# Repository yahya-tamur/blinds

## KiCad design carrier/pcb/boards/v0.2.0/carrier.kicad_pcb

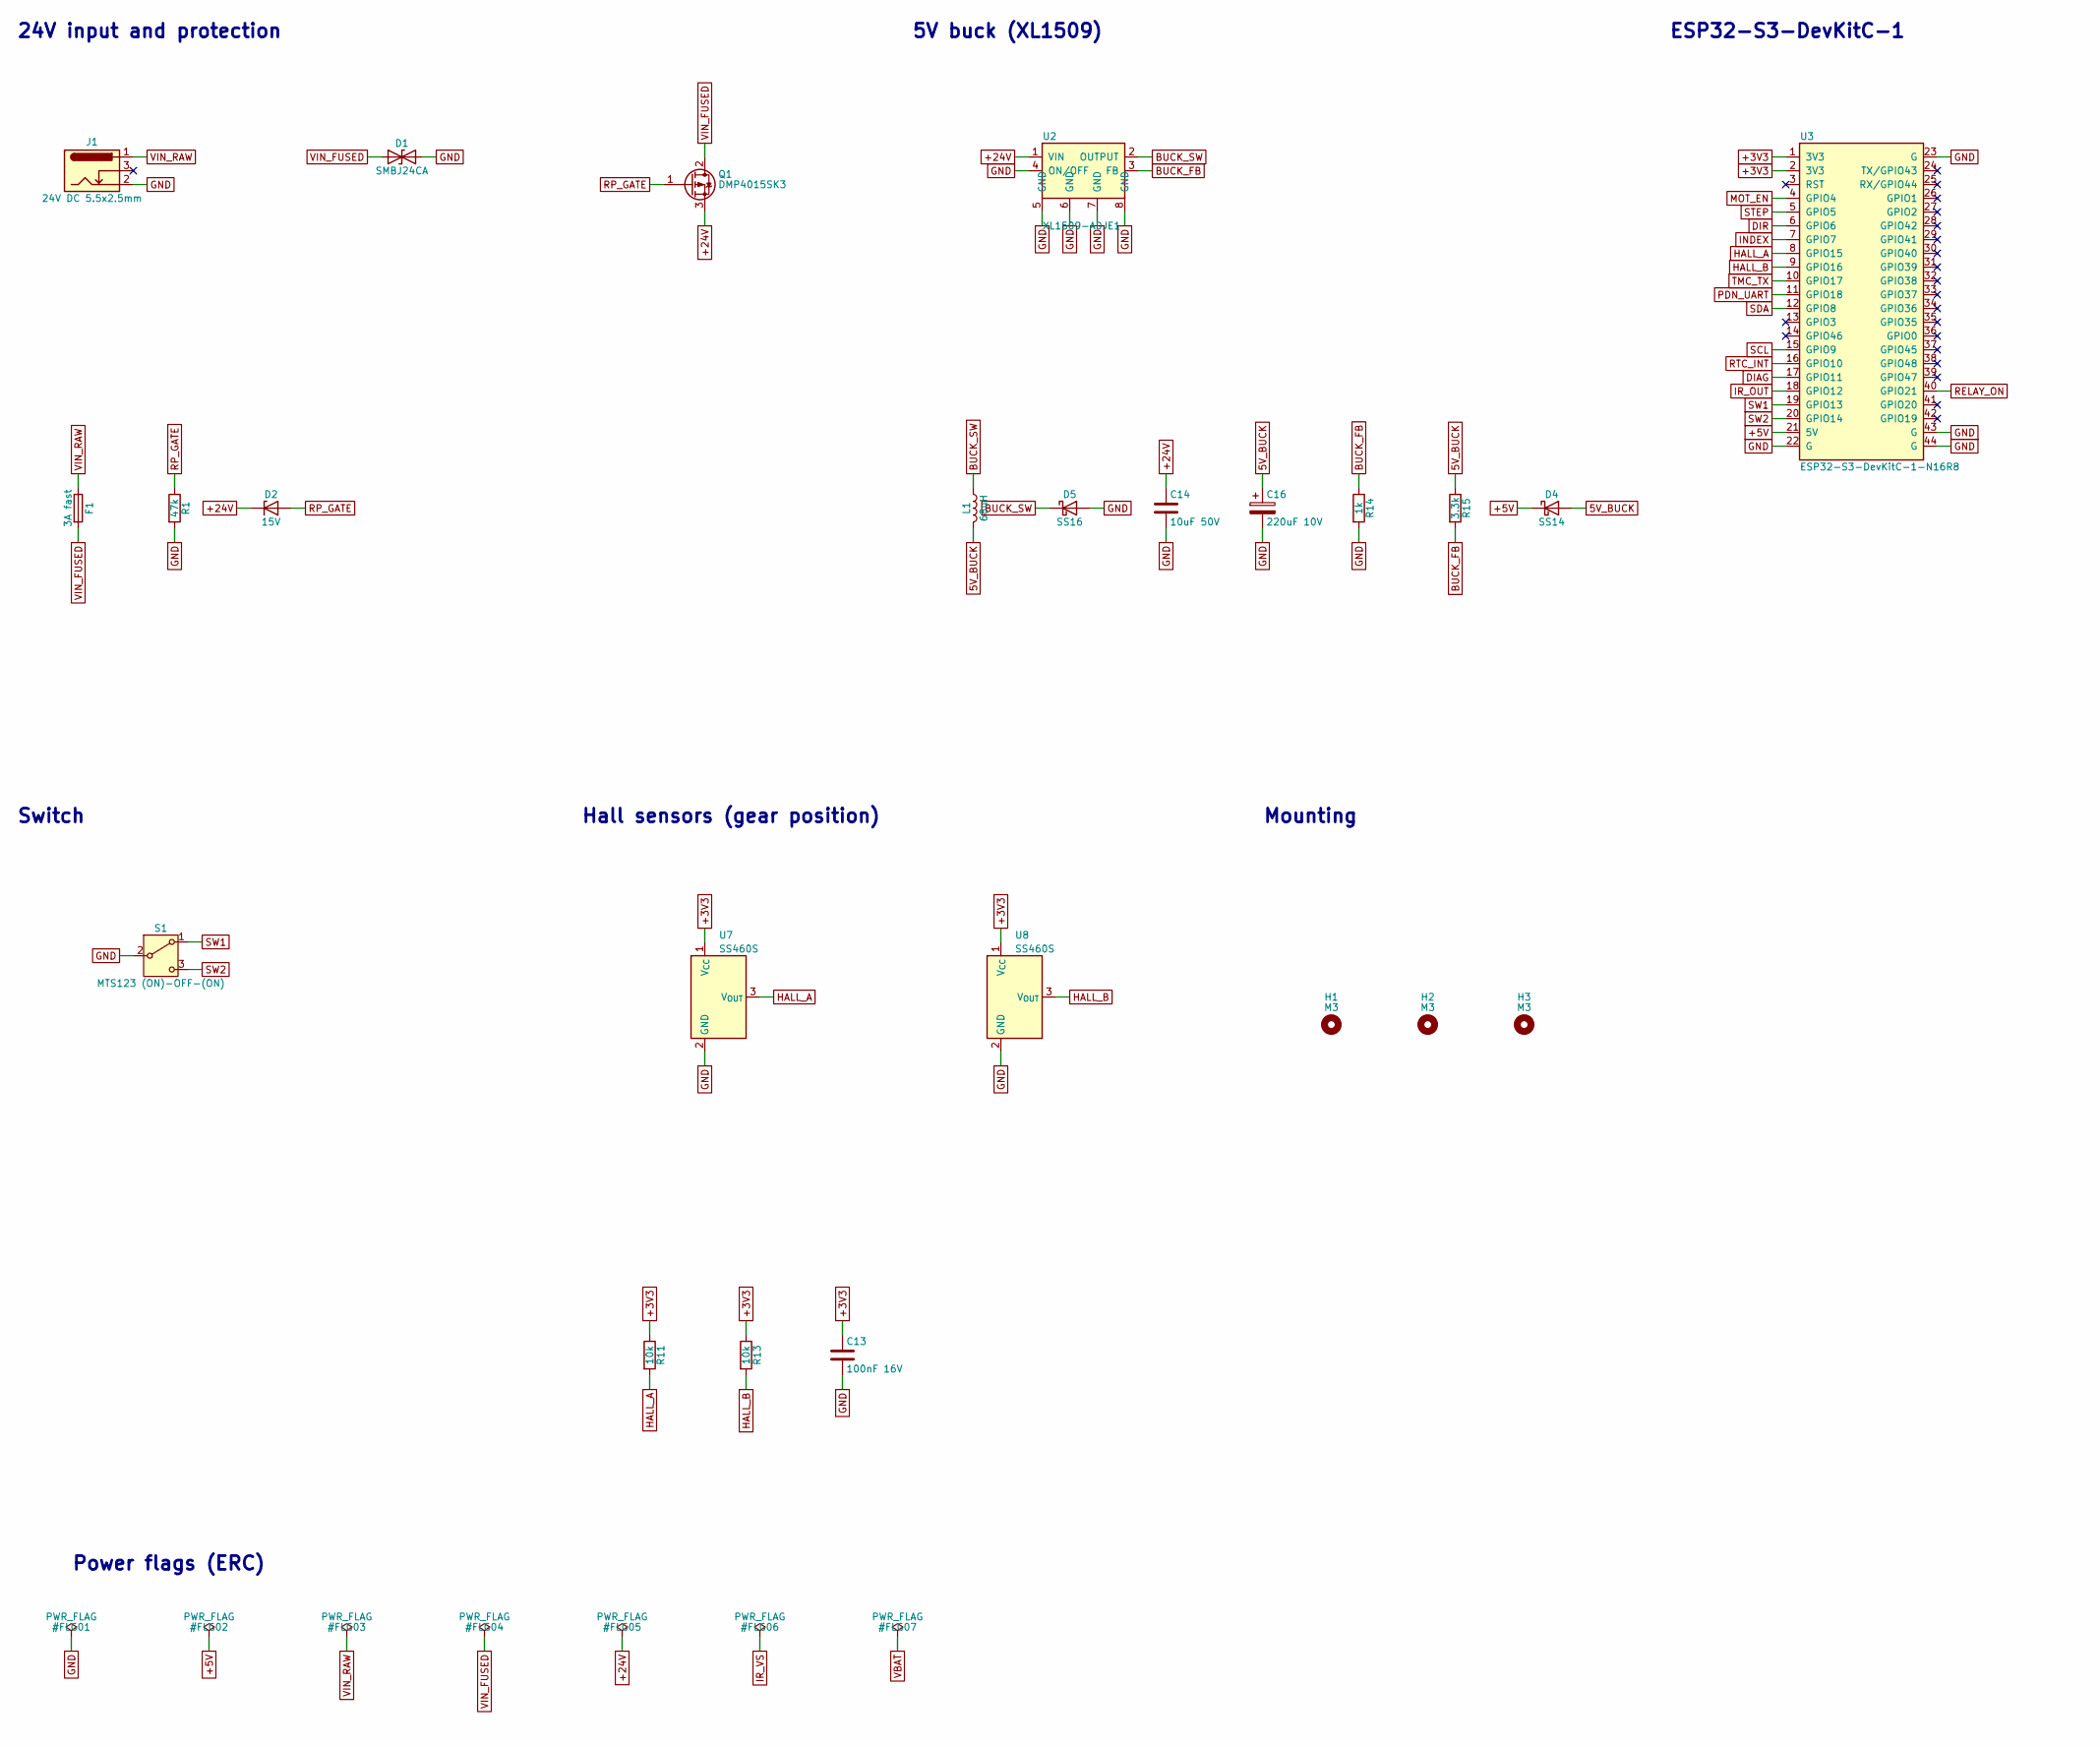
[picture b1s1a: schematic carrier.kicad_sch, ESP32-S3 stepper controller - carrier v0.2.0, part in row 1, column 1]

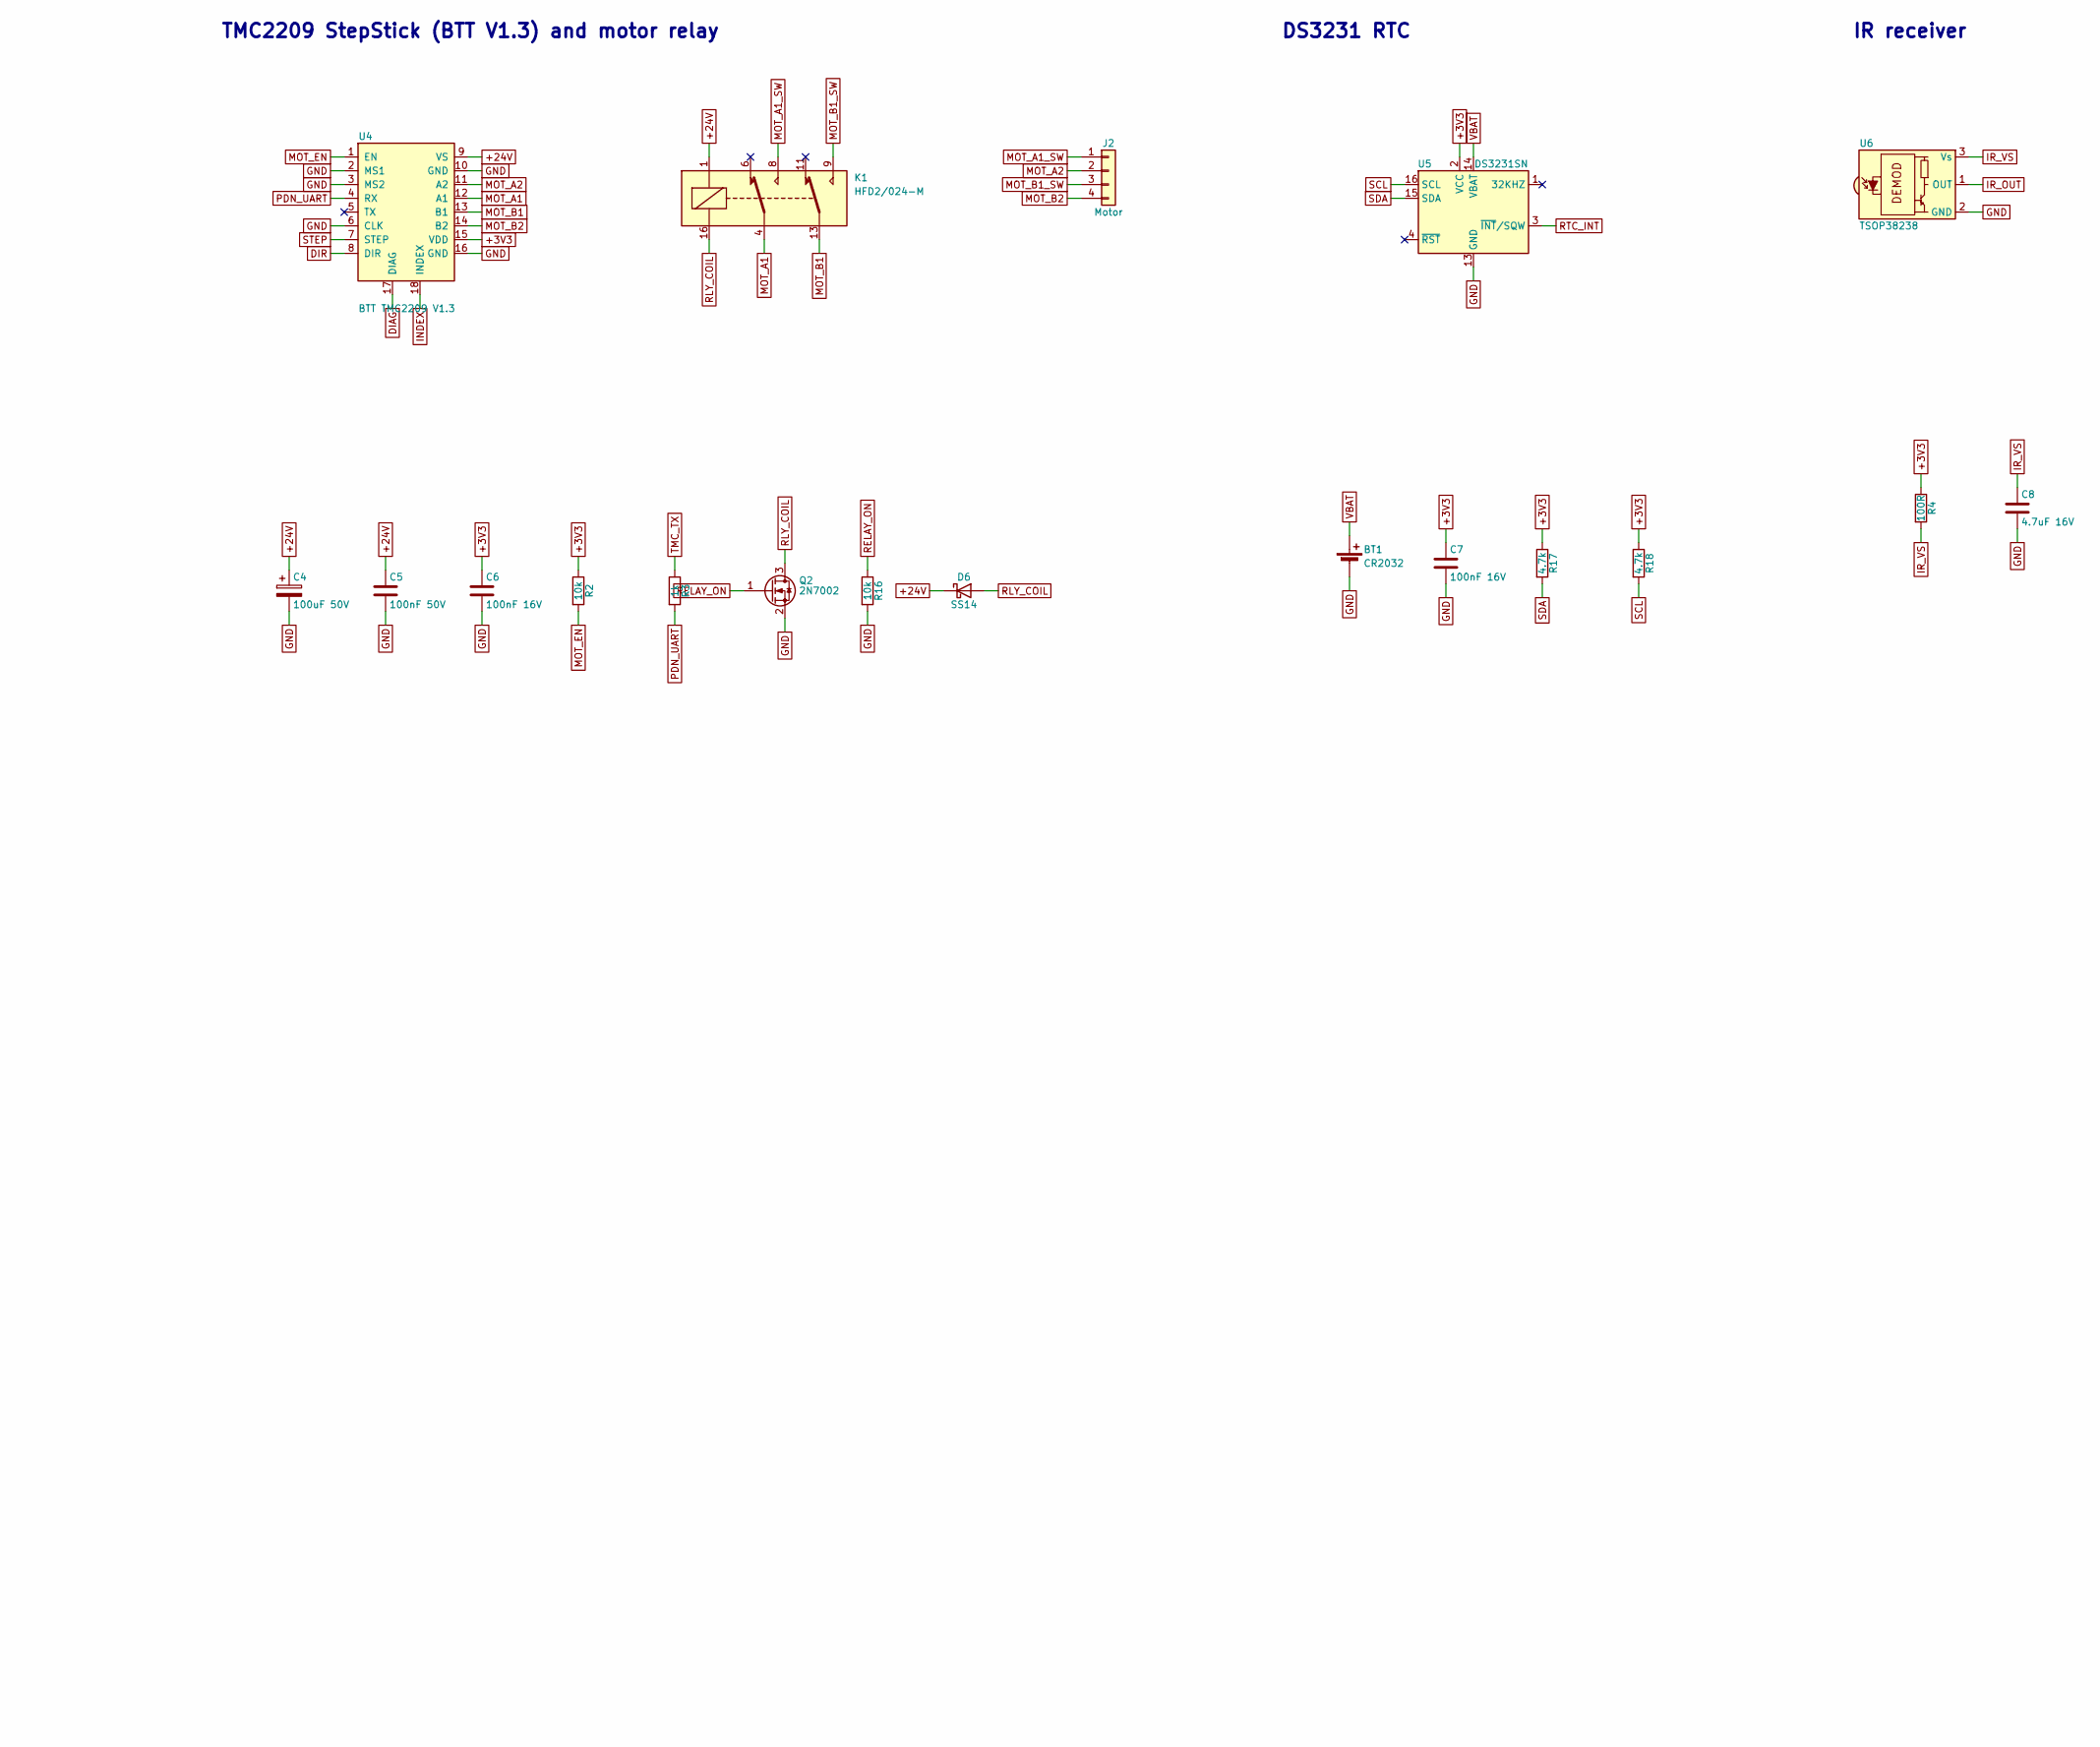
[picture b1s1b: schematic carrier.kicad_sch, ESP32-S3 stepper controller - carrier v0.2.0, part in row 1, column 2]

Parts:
BT1: CR2032; BatteryHolder_MYOUNG_BS-02-A1AJ010; MPN BS-02-A1AJ010; LCSC C5239862
C4: 100uF 50V; CP_Elec_8x10; MPN EEE-FK1H101P; LCSC C178548
C5: 100nF 50V; C_0805_2012Metric; LCSC C49678
C6, C7, C13: 100nF 16V; C_0805_2012Metric; LCSC C49678
C8: 4.7uF 16V; C_0805_2012Metric; LCSC C1779
C14: 10uF 50V; C_1210_3225Metric; MPN CL32B106KBJNNNE; LCSC C138687
C16: 220uF 10V; CP_Elec_6.3x5.4; MPN FVH010ADA221M0654; LCSC C7469982
D1: SMBJ24CA; D_SMB; MPN SMBJ24CA; LCSC C83268
D2: 15V; D_SOD-123; MPN MMSZ5245B; LCSC C2126
D4, D6: SS14; D_SMA; MPN SS14; LCSC C2480
D5: SS16; D_SMA; MPN SS16; LCSC C2481
F1: 3A fast; Fuse_Littelfuse-NANO2-451_453; MPN 0453003.MR; LCSC C178991
H1, H2, H3: M3; MountingHole_3.2mm_M3
J1: 24V DC 5.5x2.5mm; BarrelJack_DC-005_2.5mm_Horizontal_EdgeMount; MPN DC-005-5A-2.5; LCSC C381115
J2: Motor; JST_XH_S4B-XH-A_1x04_P2.50mm_Horizontal; MPN S4B-XH-A; LCSC C157925
K1: HFD2/024-M; Relay_DPDT_Hongfa_HFD2; MPN HFD2/024-M; LCSC C18198081
L1: 68uH; L_Changjiang_FNR6045S; MPN FNR6045S680MT; LCSC C168091
Q1: DMP4015SK3; TO-252-2; MPN DMP4015SK3-13; LCSC C513222
Q2: 2N7002; SOT-23; MPN 2N7002; LCSC C8545
R1: 47k; R_0805_2012Metric; LCSC C17713
R2, R11, R13, R16: 10k; R_0805_2012Metric; LCSC C17414
R3, R14: 1k; R_0805_2012Metric; LCSC C17513
R4: 100R; R_0805_2012Metric; LCSC C17408
R15: 3.3k; R_0805_2012Metric; LCSC C26010
R17, R18: 4.7k; R_0805_2012Metric; LCSC C17673
S1: MTS123 (ON)-OFF-(ON); Switch_CAX_MTS123_D2; MPN CAX-MTS123-D2-BKJL; LCSC C55072606
U2: XL1509-ADJE1; SOIC-8_3.9x4.9mm_P1.27mm; MPN XL1509-ADJE1; LCSC C74192
U3: ESP32-S3-DevKitC-1-N16R8; ESP32-S3-DevKitC-1_Soldered; MPN ESP32-S3-DevKitC-1-N16R8
U4: BTT TMC2209 V1.3; StepStick_BTT_TMC2209_Soldered; MPN BIGTREETECH TMC2209 V1.3
U5: DS3231SN; SOIC-16W_7.5x10.3mm_P1.27mm; MPN DS3231SN#T&R; LCSC C9866
U6: TSOP38238; IR_Receiver_3Pin_LyingFlat; MPN TSOP38238; LCSC C141632
U7, U8: SS460S; TO-92S; MPN SS460S; LCSC C111925

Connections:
5V_BUCK: C16.1, D4.2 (A), L1.2, R15.1
+3V3: C6.1, C7.1, C13.1, R2.1, R4.1, R11.1, R13.1, R17.1, R18.1, U3.1 (3V3), U3.2 (3V3), U4.15 (VDD), U5.2 (VCC), U7.1 (V_{CC}), U8.1 (V_{CC})
+5V: D4.1 (K), U3.21 (5V)
+24V: C4.1, C5.1, C14.1, D2.1 (K), D6.1 (K), K1.1, Q1.3 (S), U2.1 (VIN), U4.9 (VS)
BUCK_FB: R14.1, R15.2, U2.3 (FB)
BUCK_SW: D5.1 (K), L1.1, U2.2 (OUTPUT)
DIAG: U3.17 (GPIO11), U4.17 (DIAG)
DIR: U3.6 (GPIO6), U4.8 (DIR)
GND: BT1.2 (-), C4.2, C5.2, C6.2, C7.2, C8.2, C13.2, C14.2, C16.2, D1.2 (A2), D5.2 (A), J1.2, Q2.2 (S), R1.2, R14.2, R16.2, S1.2 (B), U2.4 (ON/OFF), U2.5 (GND), U2.6 (GND), U2.7 (GND), U2.8 (GND), U3.22 (G), U3.23 (G), U3.43 (G), U3.44 (G), U4.2 (MS1), U4.3 (MS2), U4.6 (CLK), U4.10 (GND), U4.16 (GND), U5.5 (GND), U5.6 (GND), U5.7 (GND), U5.8 (GND), U5.9 (GND), U5.10 (GND), U5.11 (GND), U5.12 (GND), U5.13 (GND), U6.2 (GND), U7.2 (GND), U8.2 (GND)
HALL_A: R11.2, U3.8 (GPIO15), U7.3 (V_{OUT})
HALL_B: R13.2, U3.9 (GPIO16), U8.3 (V_{OUT})
INDEX: U3.7 (GPIO7), U4.18 (INDEX)
IR_OUT: U3.18 (GPIO12), U6.1 (OUT)
IR_VS: C8.1, R4.2, U6.3 (Vs)
MOT_A1: K1.4, U4.12 (A1)
MOT_A1_SW: J2.1, K1.8
MOT_A2: J2.2, U4.11 (A2)
MOT_B1: K1.13, U4.13 (B1)
MOT_B1_SW: J2.3, K1.9
MOT_B2: J2.4, U4.14 (B2)
MOT_EN: R2.2, U3.4 (GPIO4), U4.1 (EN)
PDN_UART: R3.2, U3.11 (GPIO18), U4.4 (RX)
RELAY_ON: Q2.1 (G), R16.1, U3.40 (GPIO21)
RLY_COIL: D6.2 (A), K1.16, Q2.3 (D)
RP_GATE: D2.2 (A), Q1.1 (G), R1.1
RTC_INT: U3.16 (GPIO10), U5.3 (~INT/SQW)
SCL: R18.2, U3.15 (GPIO9), U5.16 (SCL)
SDA: R17.2, U3.12 (GPIO8), U5.15 (SDA)
STEP: U3.5 (GPIO5), U4.7 (STEP)
SW1: S1.1 (A), U3.19 (GPIO13)
SW2: S1.3 (C), U3.20 (GPIO14)
TMC_TX: R3.1, U3.10 (GPIO17)
VBAT: BT1.1 (+), U5.14 (VBAT)
VIN_FUSED: D1.1 (A1), F1.2, Q1.2 (D)
VIN_RAW: F1.1, J1.1

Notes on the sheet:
24V input and protection
5V buck (XL1509)
ESP32-S3-DevKitC-1
TMC2209 StepStick (BTT V1.3) and motor relay
DS3231 RTC
IR receiver
Switch
Hall sensors (gear position)
Mounting
Power flags (ERC)

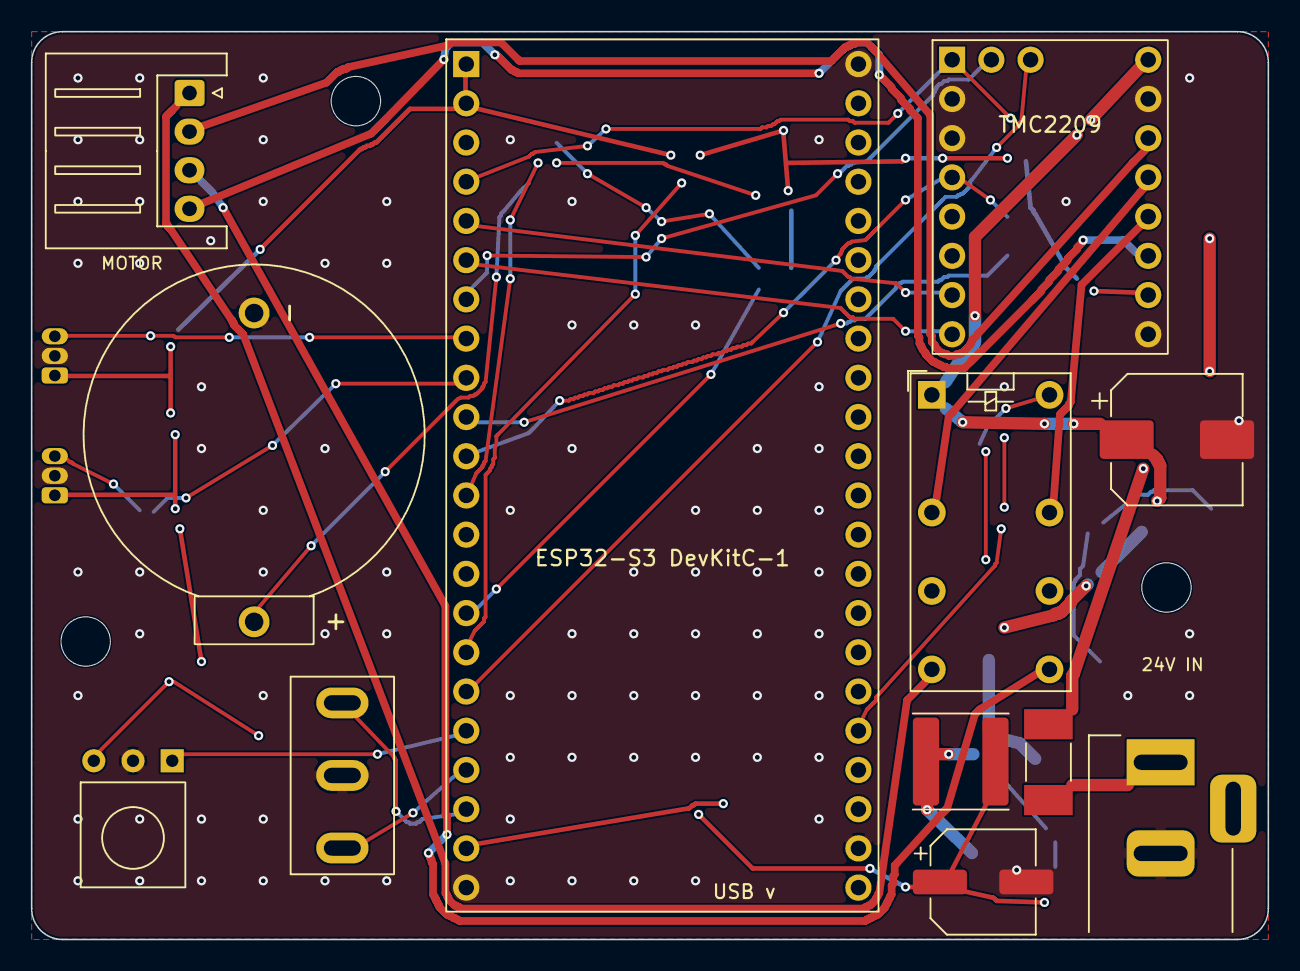
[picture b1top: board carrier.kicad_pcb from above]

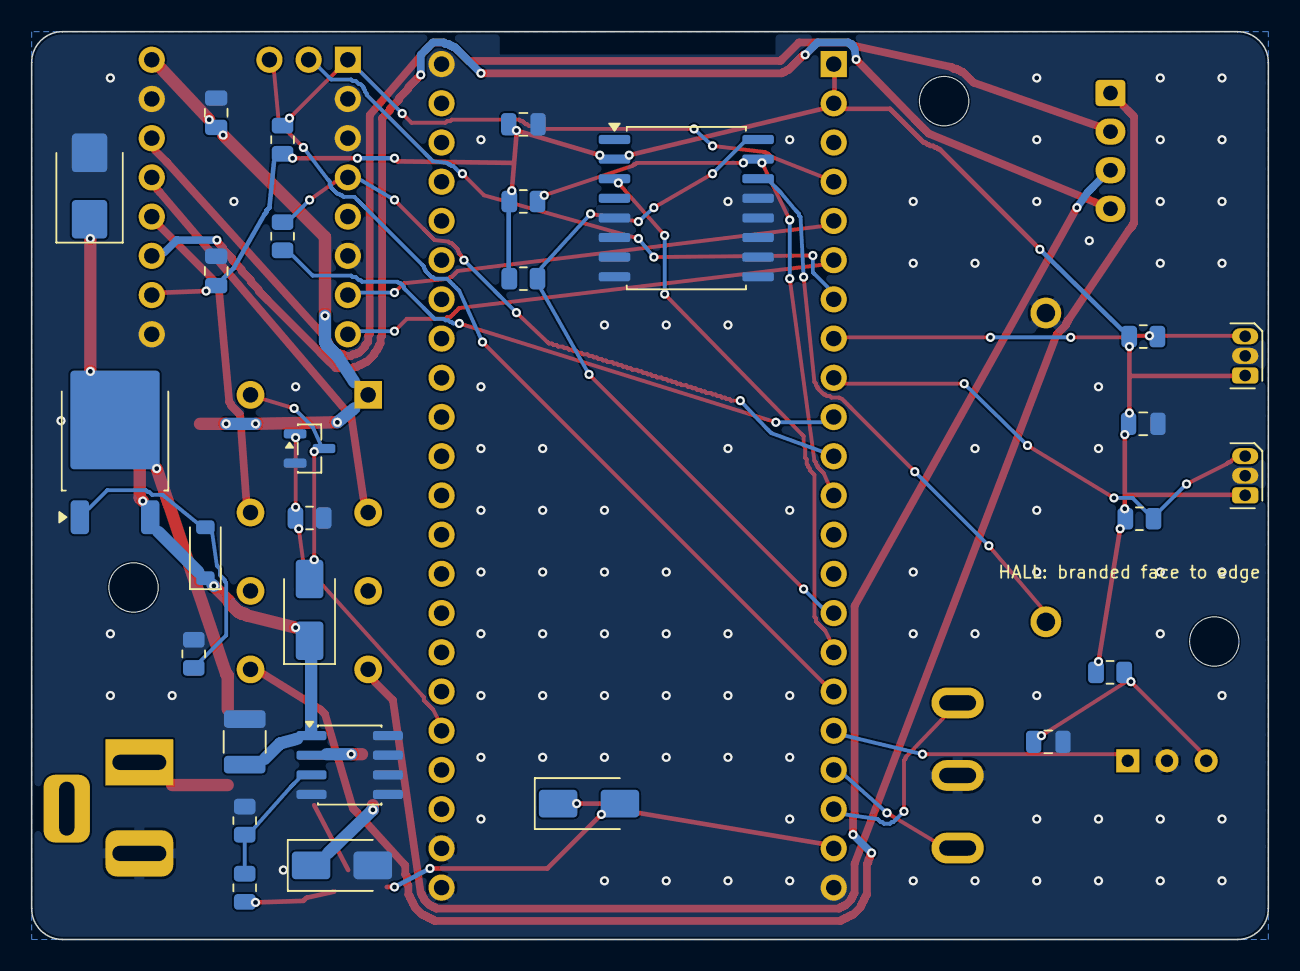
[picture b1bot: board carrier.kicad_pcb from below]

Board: 2 copper layers, 80.1 x 58.8 mm, 43 parts (28 on the bottom side), 35 nets.

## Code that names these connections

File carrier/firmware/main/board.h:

// Carrier board pin map (ESP32-S3-DevKitC-1 GPIO numbers), v0.2.0. The same pins work on v0.1.0, where GPIO21
// is not connected and the internal pull-ups sit alongside the board's.
#pragma once

#define PIN_MOT_EN   4    // TMC2209 EN, active low, 10k pull-up keeps the motor off at boot
#define PIN_STEP     5
#define PIN_DIR      6
#define PIN_INDEX    7    // TMC2209 INDEX output
#define PIN_SDA      8    // DS3231 (4.7k pull-ups on the board)
#define PIN_SCL      9
#define PIN_RTC_SQW  10   // DS3231 SQW/INT, open drain, needs the internal pull-up
#define PIN_DIAG     11   // TMC2209 DIAG output (StallGuard), high = stall or error
#define PIN_IR       12   // TSOP38238 output, low while it sees 38 kHz (~30k pull-up inside, plus the internal one)
#define PIN_SW1      13   // momentary switch to GND, straight to the pin: needs the internal pull-up
#define PIN_SW2      14
#define PIN_HALL_A   15   // Hall sensor A (open collector), on the board with a 10k pull-up
#define PIN_HALL_B   16   // Hall sensor B, the same
#define PIN_TMC_TX   17   // UART1 TX, through 1k to PDN_UART
#define PIN_TMC_RX   18   // UART1 RX, direct to PDN_UART (single-wire bus)
#define PIN_RELAY    21   // motor relay K1, high = motor connected (10k pull-down keeps it off at boot)

#define TMC_UART     UART_NUM_1
#define TMC_ADDR     0       // MS1 = MS2 = GND
#define TMC_RSENSE   0.11f   // BTT TMC2209 V1.3 sense resistors, ohms

// YEJMKJ 60 mm NEMA 17: 2.3 A/phase, 1.5 ohm, 2.8 mH, 84 Ncm holding torque.
// 1.7 A RMS (~75 % of rating, close to this driver's 1.77 A ceiling) for short bursts of motion.
// Hold current is a quarter of that; disable the driver (EN high) between moves if nothing needs holding.
// The relay only switches while EN is high, so its contacts never break the coil current:
// EN high, relay on, RELAY_SETTLE_MS, EN low ... run ... EN high, RELAY_SETTLE_MS, relay off.
#define RELAY_SETTLE_MS 10   // HFD2 operate/release time is under 5 ms
#define MOTOR_IRMS   1.7f
